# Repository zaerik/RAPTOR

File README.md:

RAPTOR
======

RAPTOR Advanced Platform for TeleOperated Reconnaissance

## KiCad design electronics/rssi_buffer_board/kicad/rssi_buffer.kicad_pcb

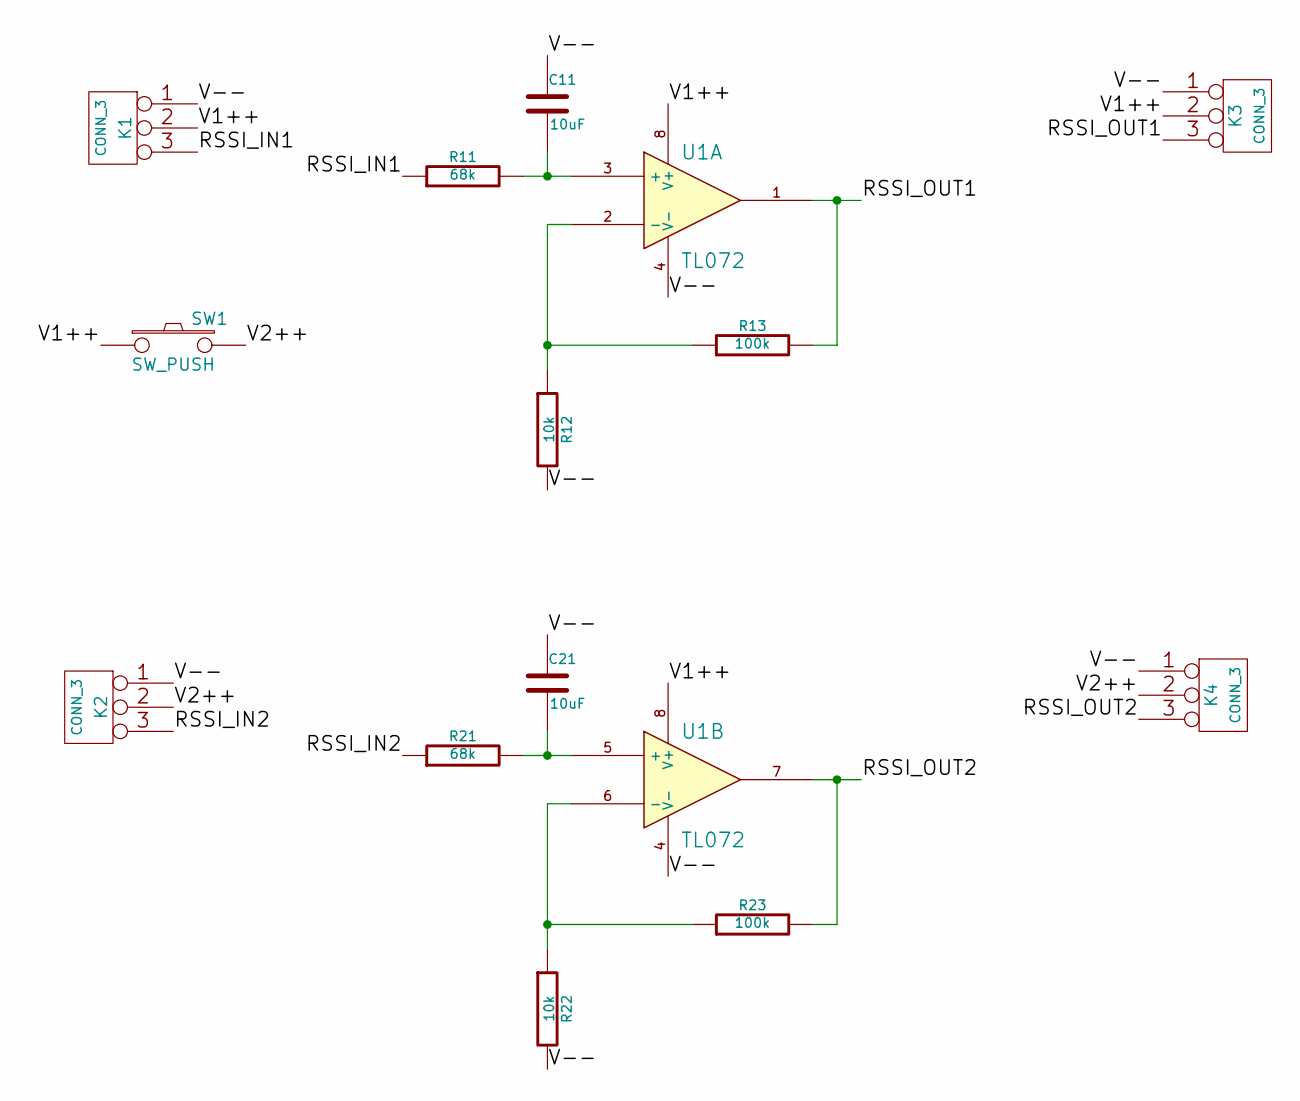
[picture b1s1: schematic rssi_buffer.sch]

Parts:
C11, C21: 10uF
K1, K2, K3, K4: CONN_3
R11, R21: 68k
R12, R22: 10k
R13, R23: 100k
SW1: SW_PUSH
U1: TL072

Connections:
/RSSI_IN1: K1.3, R11.1
/RSSI_IN2: K2.3, R21.1
/RSSI_OUT1: K3.3, R13.2, U1.1
/RSSI_OUT2: K4.3, R23.2, U1.7
/V1++: K1.2 (PM), K3.2 (PM), SW1.1, U1.8 (V+)
/V2++: K2.2 (PM), K4.2 (PM), SW1.2
/V--: C11.1, C21.1, K1.1, K2.1, K3.1, K4.1, R12.2, R22.2, U1.4 (V-)
unnamed: R22.1, R23.1, U1.6 (-)
unnamed: C21.2, R21.2, U1.5 (+)
unnamed: C11.2, R11.2, U1.3 (+)
unnamed: R12.1, R13.1, U1.2 (-)

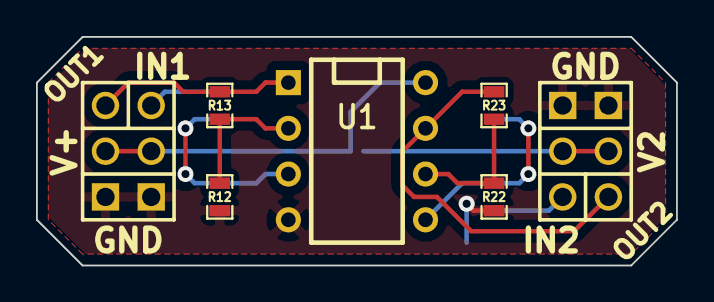
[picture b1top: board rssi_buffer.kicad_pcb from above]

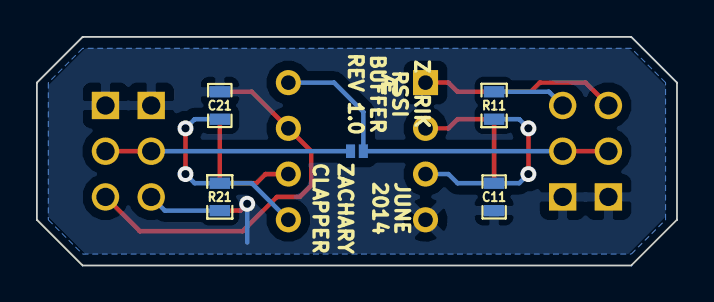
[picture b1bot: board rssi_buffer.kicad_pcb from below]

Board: 2 copper layers, 35.6 x 12.7 mm, 14 parts (5 on the bottom side), 11 nets.

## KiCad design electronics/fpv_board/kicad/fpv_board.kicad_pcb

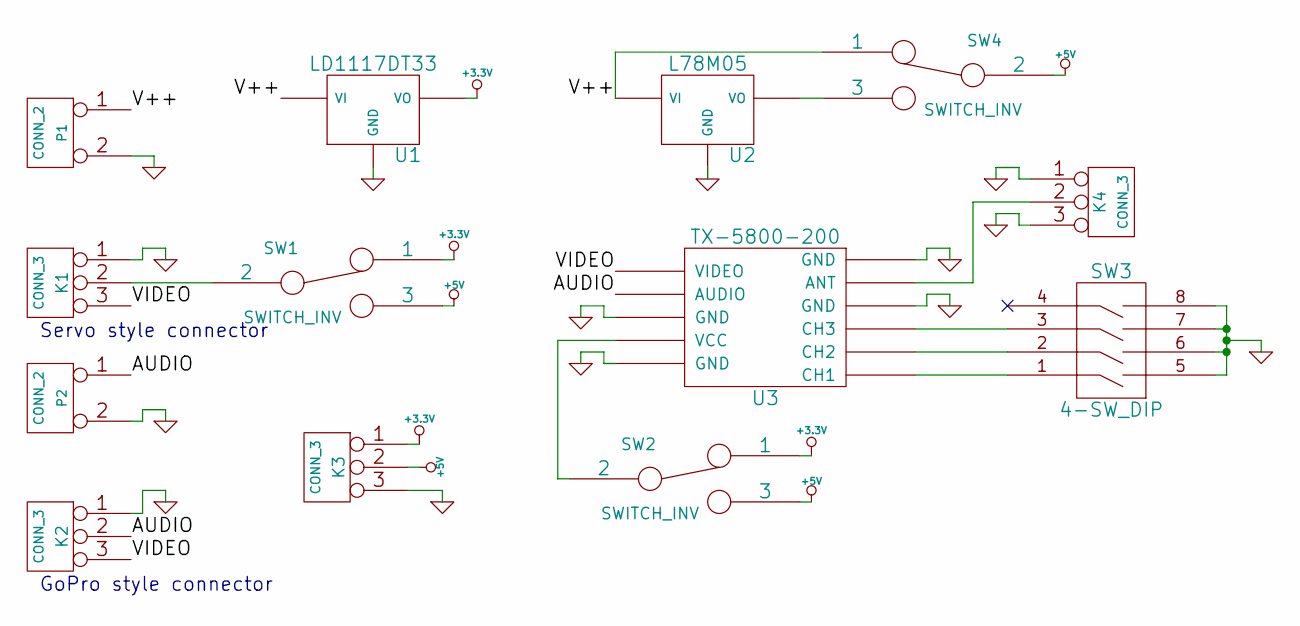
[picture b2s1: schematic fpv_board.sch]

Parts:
K1, K2, K3, K4: CONN_3
P1, P2: CONN_2
SW1, SW2, SW4: SWITCH_INV
SW3: 4-SW_DIP
U1: LD1117DT33
U2: L78M05
U3: TX-5800-200

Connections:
+3.3V: K3.1, SW1.1, SW2.1, U1.VO
+5V: K3.2 (PM), SW1.3, SW2.3, SW4.2
/AUDIO: K2.2 (PM), P2.1, U3.2 (AUDIO)
/V++: P1.1, SW4.1, U1.VI, U2.VI
/VIDEO: K1.3, K2.3, U3.1 (VIDEO)
GND: K1.1, K2.1, K3.3, K4.1, K4.3, P1.2 (PM), P2.2 (PM), SW3.5, SW3.6, SW3.7, SW3.8, U1.GND, U2.GND, U3.3 (GND), U3.5 (GND), U3.9 (GND), U3.11 (GND); also elsewhere on the board
unnamed: SW3.2, U3.7 (CH2)
unnamed: SW3.1, U3.6 (CH1)
unnamed: SW3.3, U3.8 (CH3)
unnamed: K4.2 (PM), U3.10 (ANT)
unnamed: SW4.3, U2.VO
unnamed: SW2.2, U3.4 (VCC)
unnamed: K1.2 (PM), SW1.2

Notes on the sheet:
GoPro style connector
Servo style connector

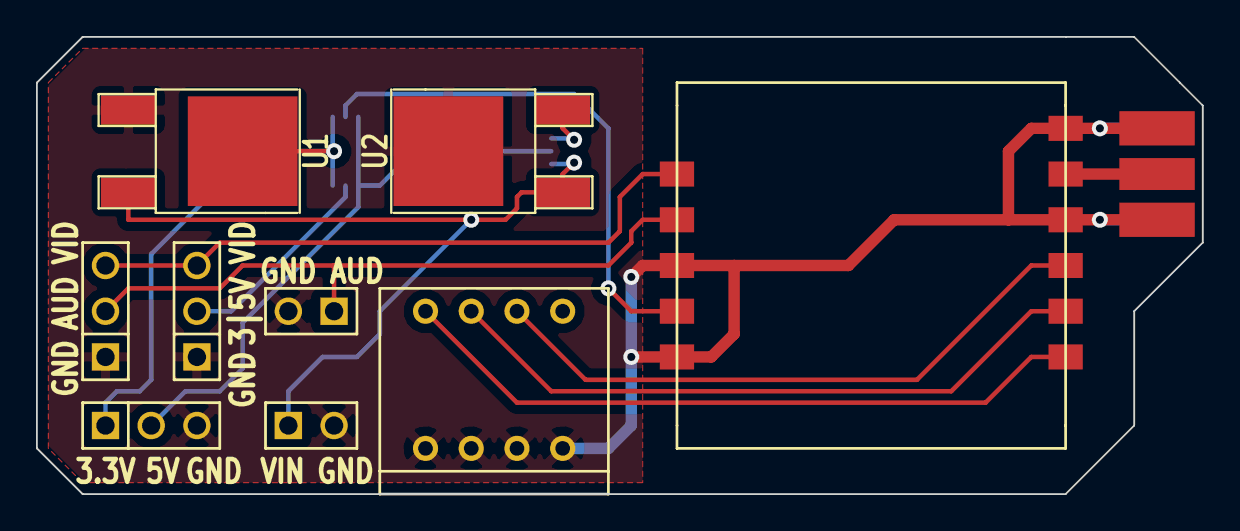
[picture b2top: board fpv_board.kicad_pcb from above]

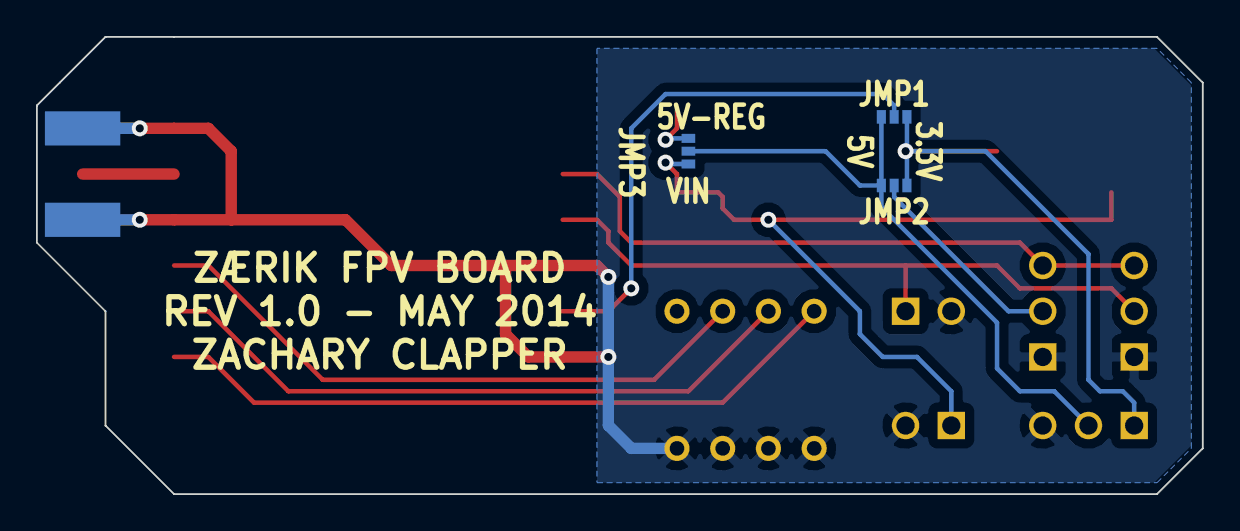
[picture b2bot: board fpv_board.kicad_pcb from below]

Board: 2 copper layers, 64.8 x 25.4 mm, 14 parts (4 on the bottom side), 13 nets.

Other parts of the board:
KB4: CONN_3; RP-SMA_board_mount_back

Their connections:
GND: KB4.1, KB4.3; also elsewhere on the board

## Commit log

2014-03-07 Update LICENSE
2014-05-25 Created FPV board schematic.
2014-05-25 Added FPV board datasheets.
2014-05-26 Updated FPV board schematic. Started implementation of FPV board PCB. Added .gitignore
2014-05-28 Added 5V source selecter jumper to FPV board schematic. Implemented FPV PCB.
2014-05-28 Added silkscreen labels to FPV PCB, also added additonal GND connection to Tx module.
2014-05-30 updated .gitignore
2014-05-30 Added description of jumpers for FPV PCB (jumpers.txt).
2014-06-23 Added RSSI Buffer Board
2017-02-05 Initial implementation of simulator for communication between flight controller and servo multiplexer board.
2017-02-11 Modified required GTK version in gui.glade
2023-11-26 Changes for Python3 compatibility. Fixed error when closing application without a serial connection.
2023-11-26 Further Python 3 compatibility changes. Removal of some decode print statements.
